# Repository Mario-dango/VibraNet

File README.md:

# Proyecto Tipo C · Red de nodos de adquisición de datos sismográficos

> Monitoreo de vibraciones/sismos en edificación universitaria con nodos ESP8266 + MPU6050, backend Node-RED/Mosquitto/MySQL en Ubuntu Server. 

---

## 1) Contexto y alcance

* **Dominio:** monitoreo sísmico estructural en la Facultad de Medicina (UNCuyo), con **4–10 nodos** distribuidos en puntos de interés. 
* **Tecnologías núcleo:** Node-RED (gestión/visualización), Mosquitto (MQTT), MySQL (persistencia), Ubuntu Server (SO). 
* **Nodo:** ESP8266 (ESP-01) + MPU6050 (GY-521), alimentación fija y Li-ion, PCB propia. 
* **Motivación:** alternativa **de bajo costo** con desempeño “accionable” frente a soluciones comerciales de alta precisión pero costosas.  

**Objetivo general:** validar la factibilidad y el error objetivo (≤10%) mediante prototipado, pruebas y calibración.  

---

## 2) Arquitectura (E2E)

```mermaid
flowchart LR
  %% IDs simples (A–Z, 0–9, _), solo ASCII. Sin <br/> ni comillas curvas.
  subgraph Capa_Nodos_4_10
    A1["ESP8266 / ESP-01\nMPU6050 (GY-521)"] -->|MQTT QoS1| BRK[(Mosquitto)]
    A2["ESP8266 / ESP-01\nMPU6050 (GY-521)"] -->|MQTT QoS1| BRK
  end

  BRK --> NR["Node-RED\nFlows + Dashboards"]
  NR  --> DB[(MySQL)]
  NR  --> A[Alertas / Notificaciones]

  %% Estilo básico para infra
  classDef infra fill:#eeeeee,stroke:#333333,stroke-width:1px;
  class BRK,DB infra;
```

**Notas:**

* Visualización y orquestación en **Node-RED**, broker **Mosquitto**, almacenamiento **MySQL** sobre **Ubuntu Server**. 
* Escalabilidad por cobertura de **4–10** dispositivos; despliegue in situ en el edificio objetivo. 

---

## 3) Estructura del repositorio

```
.
├─ firmware/                # Código ESP8266 (ESP-01) + MPU6050
   ├─ src/
   └─ include/
├─ design/                  # 3D models
│  ├─ Acoples/              
│  ├─ Accesorios/                 
│  └─ Impresiones 3D/                   
├─ PCB/
│  └─ Diseño de módulo      
├─ docs/
│  ├─ arquitectura.md
│  ├─ calibracion.md
│  └─ o&m.md
└─ README.md
```

---

## 4) Requisitos

* **Nodo:** Módulo ESP-07, módulo GY-521, fuente 5 V + step-down 3.3 V, batería Li-ion opcional. 
* **Servidor:** Ubuntu Server con Node-RED, Mosquitto y MySQL. 

---

## 5) Firmware (ESP8266 + MPU6050)

**Intención:** lectura de aceleraciones/giroscopio, timestamp NTP, buffer local, MQTT QoS1 con reconexión y LWT, watchdog, empaquetado JSON/CBOR.

**Supuestos de diseño:**

* Frecuencia de muestreo recomendada 100–200 Hz para vibraciones estructurales de baja a media frecuencia.
* Antialiasing digital simple con media móvil/BIQUAD; calibración in situ en etapa de instalación.

**Esqueleto de payload (JSON):**

```json
{
  "node_id": "FACMED-03",
  "ts_unix_ms": 1733345678901,
  "ax": -0.0123, "ay": 0.0045, "az": 1.0012,
  "gx": 0.12, "gy": -0.05, "gz": 0.02,
  "vbat": 3.94, "temp": 28.4, "seq": 15231
}
```

**Tópicos MQTT:**

```
sismo/nodo/<node_id>/datos       (QoS1, no retenido)
sismo/nodo/<node_id>/estado      (QoS1, retenido)      # heartbeats
sismo/nodo/<node_id>/lwt         (QoS1, retenido)      # Last Will
sismo/cmd/<node_id>              (QoS1)                # control
```

**Criterios de prueba rápida:**

1. Pérdida de WiFi: datos en buffer y reenvío al reconectar.
2. Desconexión broker: activación de **LWT** y recuperación de sesión.
3. Variación NTP: jitter de timestamp < 20 ms en red local.

---

## 6) Backend

### 6.1 Mosquitto (MQTT)

**Intención:** broker central con TLS, usuarios/ACL y LWT.

```conf
# deploy/mqtt/mosquitto.conf (resumen)
listener 8883
cafile /etc/mosquitto/certs/ca.crt
certfile /etc/mosquitto/certs/server.crt
keyfile /etc/mosquitto/certs/server.key
require_certificate false
allow_anonymous false
password_file /etc/mosquitto/passwd
acl_file /etc/mosquitto/acl
persistence true
persistence_location /var/lib/mosquitto/
```

**ACL mínimo de ejemplo:**

```
user nodo01
topic write sismo/nodo/nodo01/#
topic read  sismo/cmd/nodo01

user nodered
topic read  sismo/nodo/+/datos
topic read  sismo/nodo/+/estado
topic read  sismo/nodo/+/lwt
topic write sismo/cmd/+
```

### 6.2 Node-RED

**Intención:** ingestión MQTT, cálculo de KPIs (PGA/PGV), alarmas y dashboard.
**KPIs sugeridos:** PGA, PGV, espectros de respuesta 5% amort.
**Entrega:** flujos exportables en `backend/nodered/flows/*.json`.

### 6.3 MySQL (modelo de datos)

**Intención:** persistencia de series temporales y metadatos.

```sql
-- backend/db/schema.sql (resumen)
CREATE TABLE nodes (
  id VARCHAR(32) PRIMARY KEY,
  alias VARCHAR(64),
  location VARCHAR(128),
  installed_at DATETIME,
  active TINYINT DEFAULT 1
);

CREATE TABLE samples (
  id BIGINT AUTO_INCREMENT PRIMARY KEY,
  node_id VARCHAR(32) NOT NULL,
  ts_unix_ms BIGINT NOT NULL,
  ax FLOAT NOT NULL, ay FLOAT NOT NULL, az FLOAT NOT NULL,
  gx FLOAT, gy FLOAT, gz FLOAT,
  vbat FLOAT, temp FLOAT, seq BIGINT,
  KEY k_node_ts (node_id, ts_unix_ms),
  CONSTRAINT fk_samples_node FOREIGN KEY (node_id) REFERENCES nodes(id)
);

CREATE TABLE events (
  id BIGINT AUTO_INCREMENT PRIMARY KEY,
  started_at DATETIME NOT NULL,
  ended_at   DATETIME,
  max_pga FLOAT, max_pgv FLOAT, note VARCHAR(255)
);
```

**Criterios de prueba rápida:**

* Inserción sostenida ≥ 200 msg/s en LAN con retardo < 100 ms E2E.
* Consultas por ventana móvil de 5 min bajo 200 ms.

---

## 7) Despliegue

### 7.1 Docker Compose (opcional)

```yaml
# deploy/docker-compose.yml
version: "3.9"
services:
  mosquitto:
    image: eclipse-mosquitto:2
    ports: ["1883:1883", "8883:8883"]
    volumes:
      - ./mqtt/mosquitto.conf:/mosquitto/config/mosquitto.conf:ro
      - ./mqtt/certs:/etc/mosquitto/certs:ro
      - mosq_data:/var/lib/mosquitto
  nodered:
    image: nodered/node-red:latest
    ports: ["1880:1880"]
    environment:
      - TZ=America/Argentina/Mendoza
    volumes:
      - ./nodered/data:/data
  mysql:
    image: mysql:8
    environment:
      - MYSQL_ROOT_PASSWORD=changeme
      - MYSQL_DATABASE=sismo
    ports: ["3306:3306"]
    volumes: [ "mysql_data:/var/lib/mysql" ]
volumes: { mosq_data: {}, mysql_data: {} }
```

### 7.2 Ubuntu Server

* Instalar paquetes base, habilitar firewall, configurar TLS y usuarios para broker y DB. 

---

## 8) Seguridad y roles

* **Transporte:** TLS en MQTT y en accesos al dashboard.
* **Autenticación:** usuarios separados por rol: `nodo`, `nodered`, `ops`.
* **Principio de mínimo privilegio:** ACL por tópico.
* **DB:** credenciales por servicio, rotación y backups programados.

---

## 9) Calibración y validación

* **Metodología:** prototipado → pruebas con estímulos conocidos → calibración para error ≤10%. 
* **Resultados esperados:** sistema instalado, base de datos operativa, informe técnico. 

---

## 10) Plan de pruebas

1. **Nodo**: watchdog, reconexión, buffer offline, precisión de timestamp.
2. **Red**: caída de WiFi y broker, recuperación de sesión MQTT.
3. **Integración**: ingestión Node-RED → MySQL, latencia y throughput.
4. **Resiliencia**: microcortes de energía, persistencia del broker.
5. **Validación**: comparación contra referencia en mesa vibratoria/estímulo controlado.

---

## 11) Instalación in situ y O&M

* **Ubicación y fijación** de nodos en la estructura; coordinación con autoridades para permisos y posiciones. 
* **Mantenimiento mínimo:** recambio/recarga de batería Li-ion según desgaste. 

---

## 12) Roadmap (alto nivel)

1. Diseño y prototipado del nodo.
2. Backend en nube y pruebas de integración.
3. Fabricación 4–10 unidades, instalación, optimización. 

---

## 13) Trazabilidad (resumen)

* **Requisito**: bajo costo y despliegue escalable → **Diseño**: ESP8266 + MPU6050; **Implementación**: MQTT/Node-RED/MySQL; **Prueba**: error ≤10%; **Resultado**: sistema instalado y DB operativa.   

---

## 14) Contribución

* PRs con tests y flujos reproducibles.
* Convenciones: commits tipo Conventional Commits, revisiones de seguridad básicas.

---

## 15) Licencia

Licencia MIT.

---

## 16) Créditos

* **Organismo:** Facultad de Ingeniería – UNCuyo. **Espacio:** Mecánica Vibratoria. 
* **Beneficiarios:** Facultad de Medicina (sistema + acceso lector a DB); cátedra Mecánica Vibratoria (nodo didáctico).  

---

## 17) Referencias del proyecto

* Documento base del proyecto: “Proyecto Tipo C: Red de nodos de adquisición de datos sismográficos.” (PDF). 
* Contexto y motivación (“Key Information”). 

---

### Anexo A · Diagrama de secuencia (telemetría)

```mermaid
sequenceDiagram
  autonumber
  participant MPU as MPU6050
  participant MCU as ESP8266 (ESP-01)
  participant BRK as Mosquitto
  participant NR as Node-RED
  participant DB as MySQL

  MPU->>MCU: Lectura ax,ay,az,gx,gy,gz @fs
  MCU->>MCU: Timestamp NTP + empaquetado JSON
  MCU->>BRK: PUBLISH sismo/nodo/<id>/datos (QoS1)
  BRK-->>NR: FORWARD mensaje
  NR->>DB: INSERT muestras
  NR-->>NR: KPIs (PGA/PGV) + alarmas
```

---

> **Cómo usar este README**
>
> 1. Adaptá el `docker-compose.yml` a tu servidor.
> 2. Importá los flujos Node-RED y conectá al broker y DB.
> 3. Flasheá el firmware del ESP-01 con tus credenciales WiFi/MQTT.
> 4. Corré pruebas de red, ingestión y calibración hasta cumplir el ≤10% de error. 

---

Medical References:
1. None — DOI: file-QWTmTeDuec8pwW5nHiFvFW

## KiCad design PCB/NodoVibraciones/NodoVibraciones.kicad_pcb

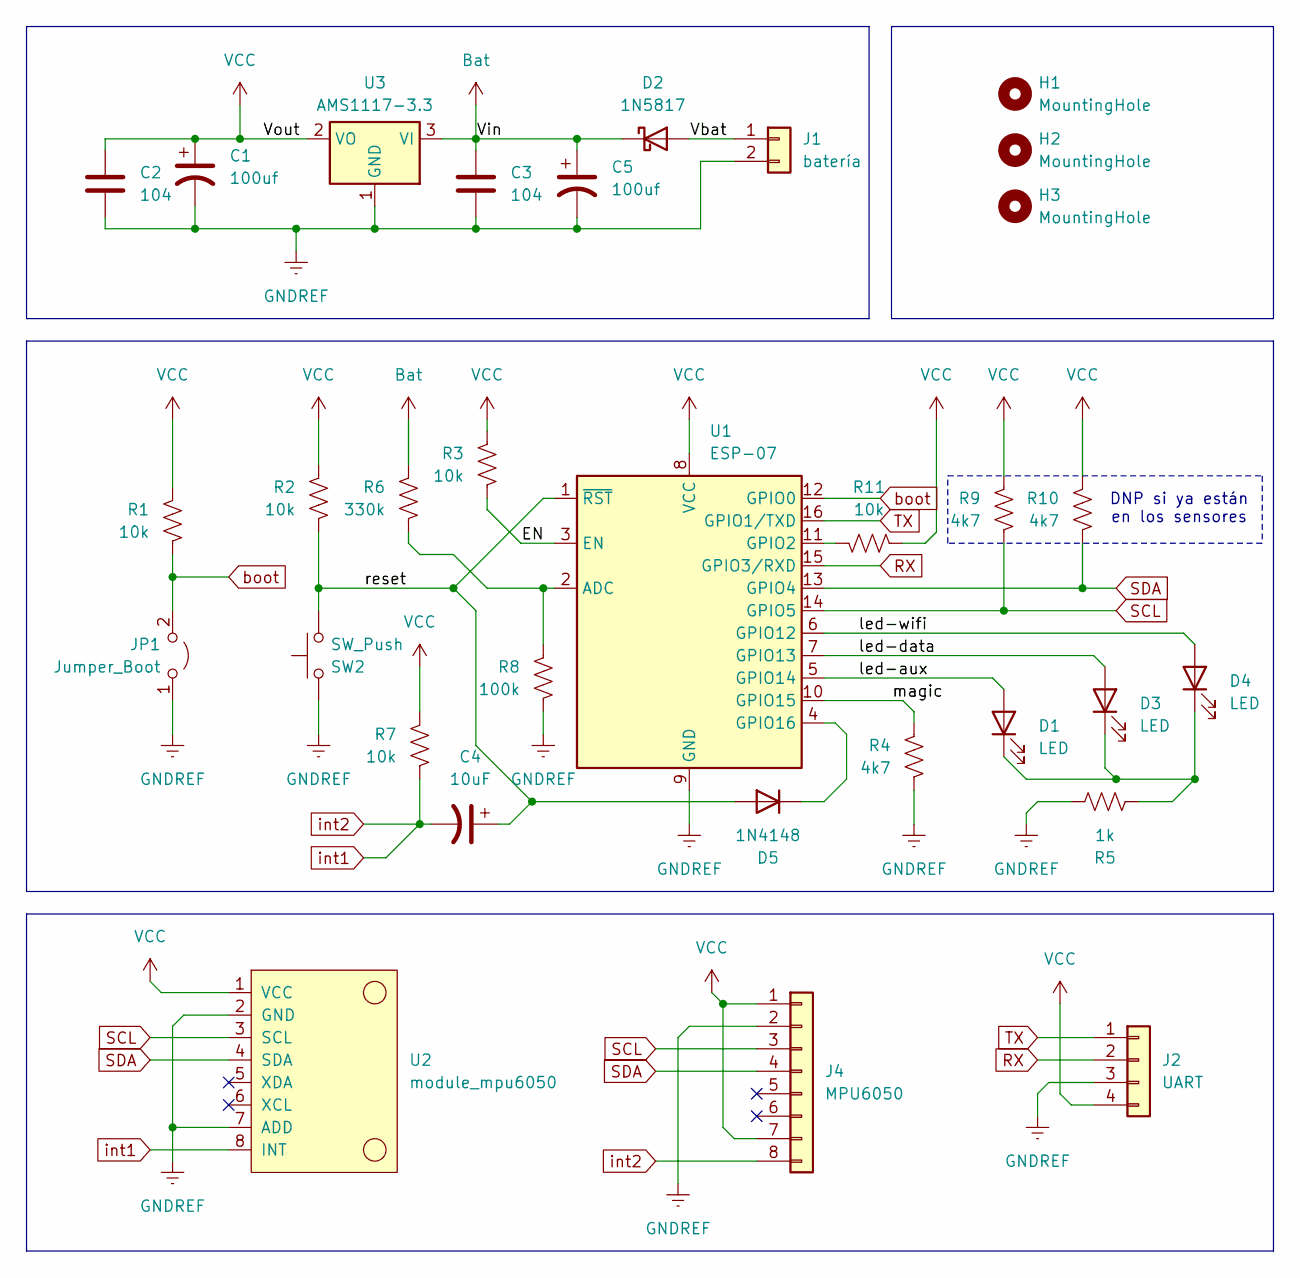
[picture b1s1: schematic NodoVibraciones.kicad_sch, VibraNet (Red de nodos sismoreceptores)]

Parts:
C1, C5: 100uf; CP_Radial_D5.0mm_P2.50mm
C2, C3: 104; C_Disc_D5.0mm_W2.5mm_P2.50mm
C4: 10uF; CP_Radial_D5.0mm_P2.50mm
D1, D3, D4: LED; LED_D5.0mm
D2: 1N5817; D_DO-41_SOD81_P10.16mm_Horizontal
D5: 1N4148; D_DO-35_SOD27_P7.62mm_Horizontal
H1, H2, H3: MountingHole; MountingHole_3.2mm_M3
J1: batería; PinHeader_1x02_P2.54mm_Horizontal
J2: UART; PinHeader_1x04_P2.54mm_Vertical
J4: MPU6050; PinSocket_1x08_P2.54mm_Vertical
JP1: Jumper_Boot; SolderJumper-2_P1.3mm_Open_RoundedPad1.0x1.5mm
R1, R2, R7, R11: 10k; R_Axial_DIN0207_L6.3mm_D2.5mm_P7.62mm_Horizontal
R3: 10k; R_Axial_DIN0207_L6.3mm_D2.5mm_P10.16mm_Horizontal
R4, R9, R10: 4k7; R_Axial_DIN0207_L6.3mm_D2.5mm_P7.62mm_Horizontal
R5: 1k; R_Axial_DIN0207_L6.3mm_D2.5mm_P7.62mm_Horizontal
R6: 330k; R_Axial_DIN0207_L6.3mm_D2.5mm_P7.62mm_Horizontal
R8: 100k; R_Axial_DIN0207_L6.3mm_D2.5mm_P7.62mm_Horizontal
SW2: SW_Push; SW_PUSH_6mm_H4.3mm
U1: ESP-07
U2: module_mpu6050
U3: AMS1117-3.3; SOT-223-3_TabPin2

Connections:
/EN: R3.1, U1.3 (EN)
/Vbat: D2.2 (A), J1.1
/led-aux: D1.2 (A), U1.5 (GPIO14)
/led-data: D3.2 (A), U1.7 (GPIO13)
/led-wifi: D4.2 (A), U1.6 (GPIO12)
/magic: R4.2, U1.10 (GPIO15)
/reset: C4.1, D5.2 (A), R2.1, SW2.1, U1.1 (~RST)
Bat: C3.1, C5.1, D2.1 (K), R6.2, U3.3 (VI)
GNDREF: C1.2, C2.2, C3.2, C5.2, J1.2, J2.3, J4.2, JP1.1 (A), R4.1, R5.2, R8.1, SW2.2, U1.9 (GND), U2.2 (GND), U2.7 (ADD), U3.1 (GND)
unnamed: D1.1 (K), D3.1 (K), D4.1 (K), R5.1
unnamed: D5.1 (K), U1.4 (GPIO16)
unnamed: R6.1, R8.2, U1.2 (ADC)
unnamed: R11.1, U1.11 (GPIO2)
RX: J2.2, U1.15 (GPIO3/RXD)
SCL: J4.3, R9.1, U1.14 (GPIO5), U2.3 (SCL)
SDA: J4.4, R10.1, U1.13 (GPIO4), U2.4 (SDA)
TX: J2.1, U1.16 (GPIO1/TXD)
VCC: C1.1, C2.1, J2.4, J4.1, J4.7, R1.2, R2.2, R3.2, R7.2, R9.2, R10.2, R11.2, U1.8 (VCC), U2.1 (VCC), U3.2 (VO)
boot: JP1.2 (B), R1.1, U1.12 (GPIO0)
int1: C4.2, J4.8, R7.1, U2.8 (INT)

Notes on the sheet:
DNP si ya están en los sensores

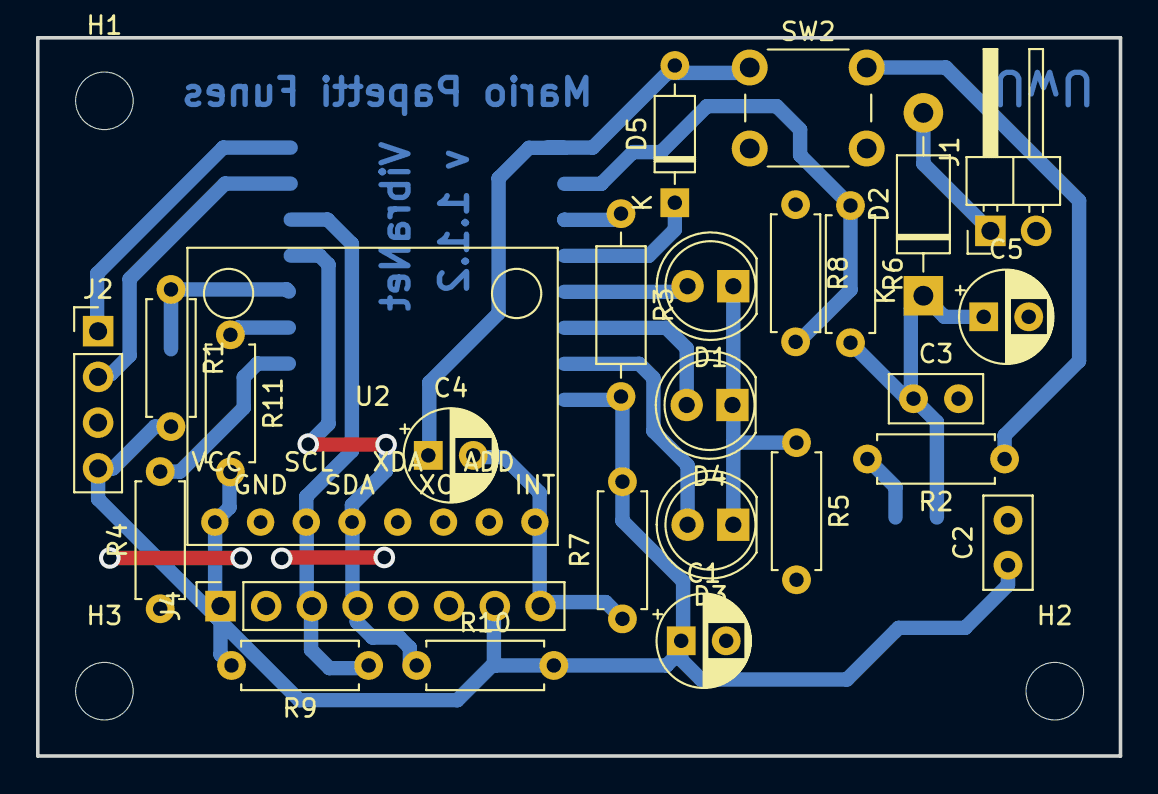
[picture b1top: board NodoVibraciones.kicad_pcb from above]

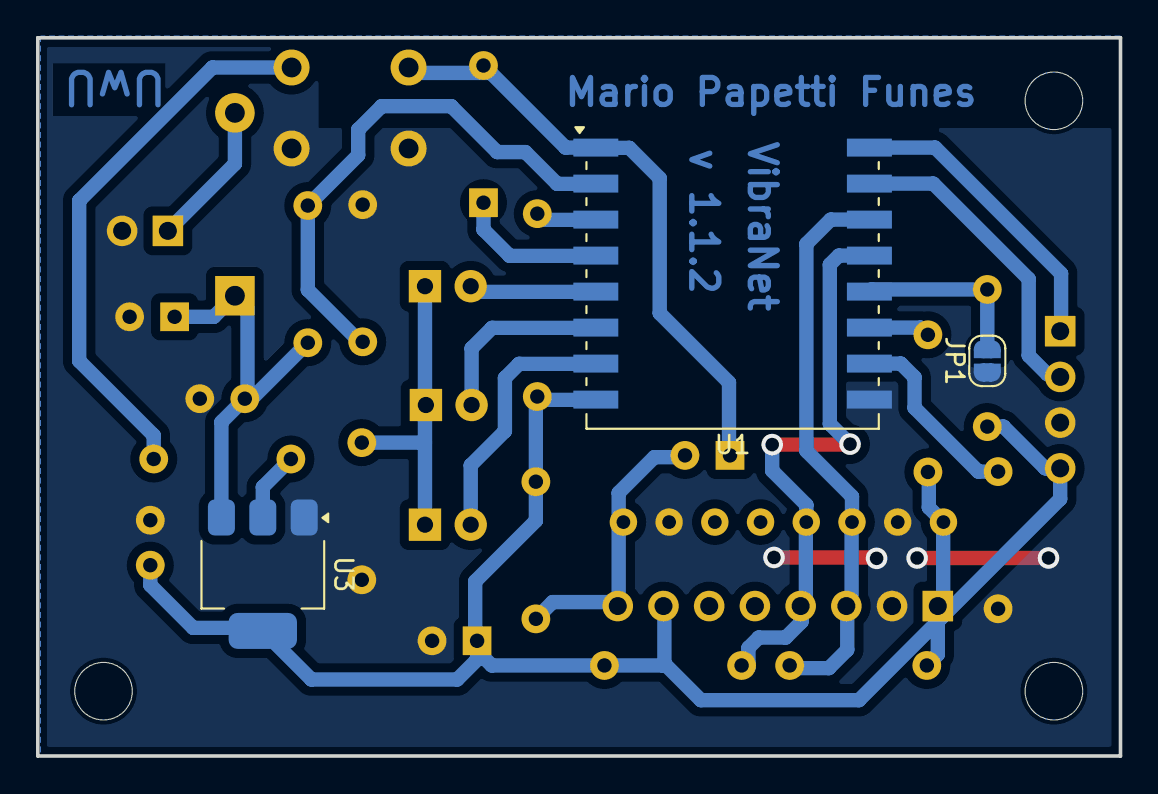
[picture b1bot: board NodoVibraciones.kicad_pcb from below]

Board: 2 copper layers, 60.1 x 39.9 mm, 33 parts (3 on the bottom side), 20 nets.

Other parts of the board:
H4: MountingHole; MountingHole_3.2mm_M3

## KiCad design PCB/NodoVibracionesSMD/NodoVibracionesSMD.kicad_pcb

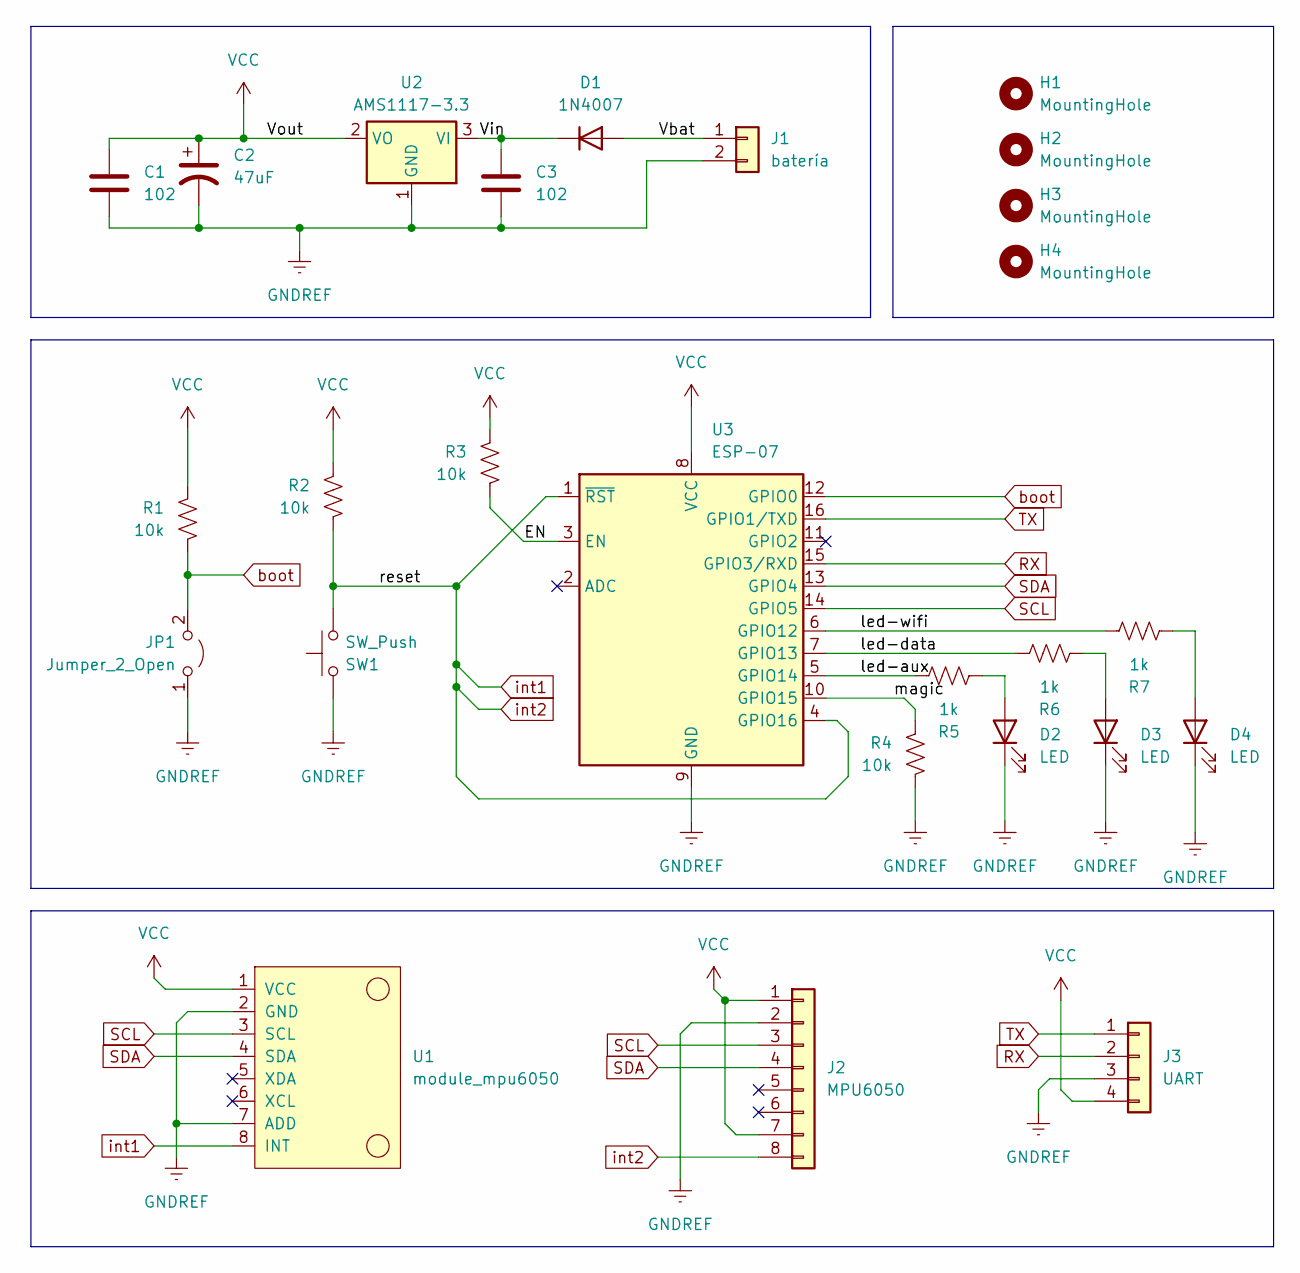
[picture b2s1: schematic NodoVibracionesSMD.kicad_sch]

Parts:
C1, C3: 102; C_1812_4532Metric_Pad1.57x3.40mm_HandSolder
C2: 47uF; CP_Elec_5x4.5
D1: 1N4007; D_SOD-123
D2, D3, D4: LED; LED_2010_5025Metric_Pad1.52x2.65mm_HandSolder
H1, H2, H3, H4: MountingHole; MountingHole_3.2mm_M3
J1: batería; PinHeader_1x02_P2.54mm_Horizontal
J2: MPU6050; PinSocket_1x08_P2.54mm_Vertical
J3: UART; PinHeader_1x04_P2.54mm_Vertical
JP1: Jumper_2_Open; SolderJumper-2_P1.3mm_Open_RoundedPad1.0x1.5mm
R1, R2, R3, R4: 10k; R_2010_5025Metric_Pad1.40x2.65mm_HandSolder
R5, R6, R7: 1k; R_2010_5025Metric_Pad1.40x2.65mm_HandSolder
SW1: SW_Push; SW_SPST_PTS645
U1: module_mpu6050
U2: AMS1117-3.3; SOT-223-3_TabPin2
U3: ESP-07

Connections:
/EN: R3.1, U3.3 (EN)
/Vbat: D1.2 (A), J1.1
/Vin: C3.1, D1.1 (K), U2.3 (VI)
/led-aux: R5.2, U3.5 (GPIO14)
/led-data: R6.2, U3.7 (GPIO13)
/led-wifi: R7.2, U3.6 (GPIO12)
/magic: R4.2, U3.10 (GPIO15)
GNDREF: C1.2, C2.2, C3.2, D2.1 (K), D3.1 (K), D4.1 (K), J1.2, J2.2, J3.3, JP1.1 (A), R4.1, SW1.2, U1.2 (GND), U1.7 (ADD), U2.1 (GND), U3.9 (GND)
unnamed: D2.2 (A), R5.1
unnamed: D3.2 (A), R6.1
unnamed: D4.2 (A), R7.1
RX: J3.2, U3.15 (GPIO3/RXD)
SCL: J2.3, U1.3 (SCL), U3.14 (GPIO5)
SDA: J2.4, U1.4 (SDA), U3.13 (GPIO4)
TX: J3.1, U3.16 (GPIO1/TXD)
VCC: C1.1, C2.1, J2.1, J2.7, J3.4, R1.2, R2.2, R3.2, U1.1 (VCC), U2.2 (VO), U3.8 (VCC)
boot: JP1.2 (B), R1.1, U3.12 (GPIO0)
int1: J2.8, R2.1, SW1.1, U1.8 (INT), U3.1 (~RST), U3.4 (GPIO16)

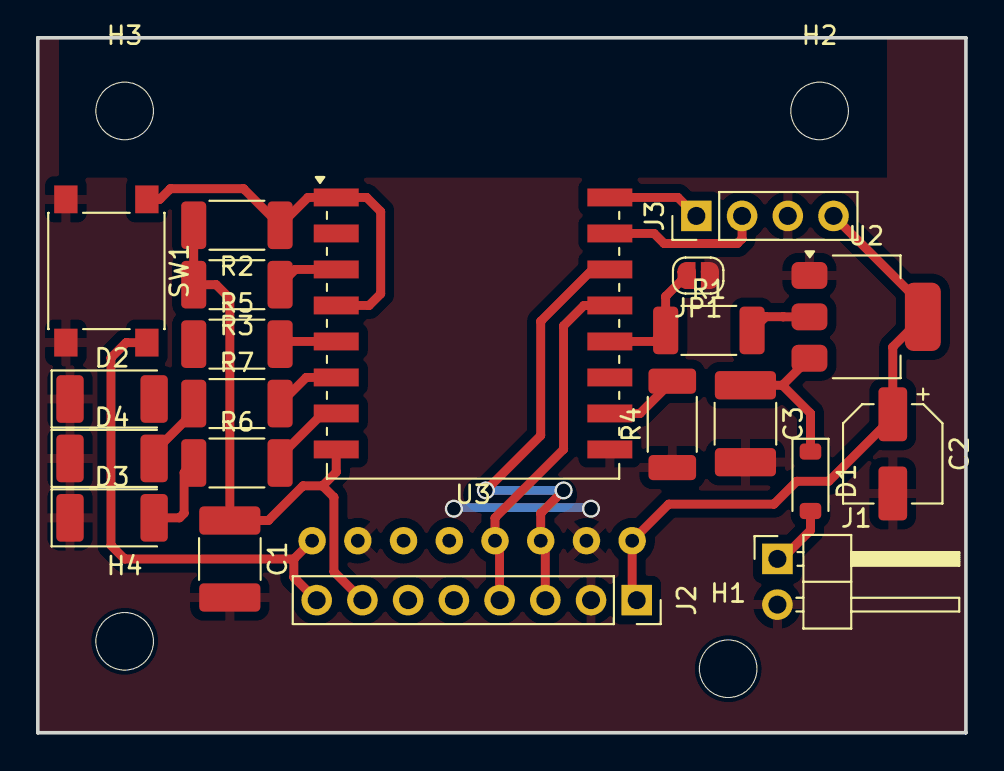
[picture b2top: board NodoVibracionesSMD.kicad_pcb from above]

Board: 2 copper layers, 51.6 x 38.6 mm, 26 parts (1 on the bottom side), 18 nets.

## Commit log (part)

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2025-10-04 Creación de estructura
2025-10-04 Rename READMe.md to README.md
2025-10-04 Se creó la carpeta de frimware
2025-10-05 Se creó PCB v0.0.1 de nodo VibraNet
2025-10-28 Se agrega archivo `Informe.ipynb`
2025-10-29 Primer avance del informe.
2025-10-29 Imágenes y primera template.
    Se suben las imágenes del avance del proyecto.
    Se decide la primera plantilla de LaTeX para el informe del avance.
2025-10-29 DataBase creada
    revisar si los campos y funcionalidades cumplen, pero se crearon las tablas:
    - cliente
    - usuario
    - sistema
    - nodo
    - mediciones
2025-10-30 Informe v2
2025-11-03 Informe de avance v1.2
2025-11-18 se agregó la carpeta node-red para trabajar con los flujos de node-red
2026-01-07 Se dockerizo Node-red, Mosquitto, InfluxDB y Grafana
2026-01-08 Se logró mandar datos a InfluxDB y visualizarlos en Grafana, también esp8266-Arduino
2026-01-09 Falta gráficos FFT (grafana), interrupciones y deepsleep (ESP8266)
2026-01-11 se actualizo docker
2026-02-02 Se implementaron interrupciones y diseño de PCB v1.0.8
2026-02-10 Lanzamiento primer prototipo funcional ESP07 verHW1.5
2026-02-22 New branch. Save point.
2026-02-22 Macros para cambiar `pinMode` y `digitalWrite`.
2026-02-22 Actualización de macros: función para resetear ESP, funciones para escribir por UART.
    Funciones de "feedback": prender LEDs para retroalimentación, restart y aviso, informar de la configuración actual.
2026-02-22 Deprecation of the branch.
2026-02-23 Primera modulacion.
    Se trasladaron todas las funciones de `main.cpp` a diferentes archivos para tener algún modicum de modularidad.
2026-02-26 Successfully modularized the whole source.
    I actually don't know HOW I did, I just know it compiles. I had to read OVER 3 DIFFERENT BOOKS, SCREW THIS.
    Anyways, we have to actually burn the µC to see if it works properly.
2026-02-26 Almost forgot this line `initMqttContext(node_id, config, client);` which could actually be fatal, as we would have been left with important pointers as nulls.
